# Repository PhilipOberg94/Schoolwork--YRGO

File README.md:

# Schoolwork--YRGO  
**Author**: Philip Öberg

## Overview  
This repository contains various schoolwork assignments and projects completed as part of my studies at YRGO. The focus of these projects is primarily on C++, Python, and C programming languages, with some projects exploring topics like machine learning and signal processing.

## Repository Structure  
The repository is structured into different directories, each containing relevant files and documentation for specific tasks:

- **ML/**: Contains files related to machine learning assignments. Current work includes a linear regression program.
- **Python/**: Contains Python programs showcasing various skills and applications.

## Projects

### Machine Learning (ML)  
- **Linear Regression Program**: A program that demonstrates basic machine learning principles using a simple linear regression model. Data import and manipulation are the main focus areas.

### Python  
- **Automation**: Python scripts for automated systems (e.g., automated horse feeder) and other utility programs.
- **Signal Processing**: Includes a frequency analysis output file (`Frekvensanalys_output.txt`) with updated value labels based on recent changes in signal processing experiments.

## Technologies Used
- C++
- Python
- C

## How to Clone the Repository

To clone the repository, run the following command:

```bash
git clone https://github.com/PhilipOberg94/Schoolwork--YRGO.git

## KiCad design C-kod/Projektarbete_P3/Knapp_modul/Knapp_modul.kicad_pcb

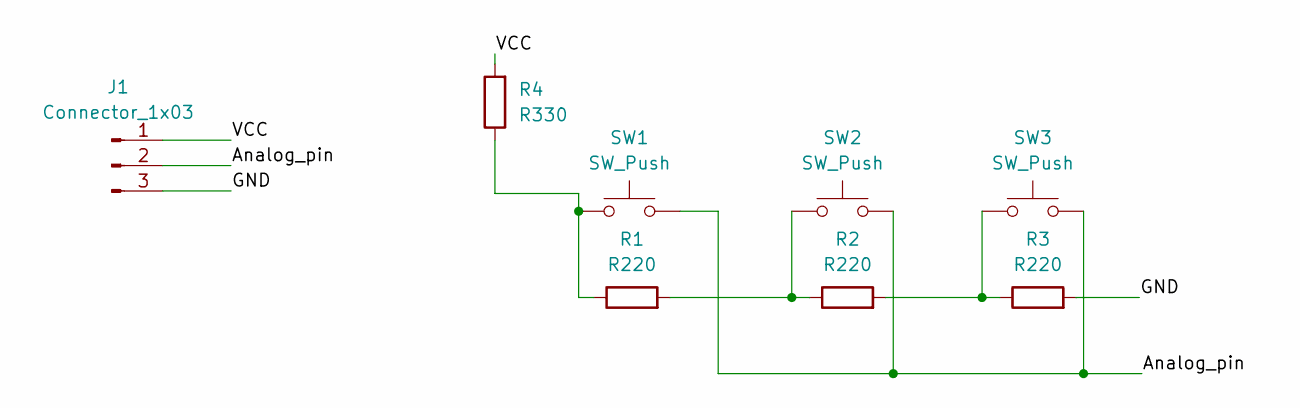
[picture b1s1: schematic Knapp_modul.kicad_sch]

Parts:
J1: Connector_1x03; PinHeader_1x03_P2.54mm_Vertical
R1, R2, R3: R220; R_Axial_DIN0207_L6.3mm_D2.5mm_P10.16mm_Horizontal
R4: R330; R_Axial_DIN0207_L6.3mm_D2.5mm_P10.16mm_Horizontal
SW1, SW2, SW3: SW_Push; LED_D5.0mm

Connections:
/Analog_pin: J1.2, SW1.2, SW2.2, SW3.2
/GND: J1.3, R3.2
/VCC: J1.1, R4.2
unnamed: R1.1, R4.1, SW1.1
unnamed: R1.2, R2.1, SW2.1
unnamed: R2.2, R3.1, SW3.1

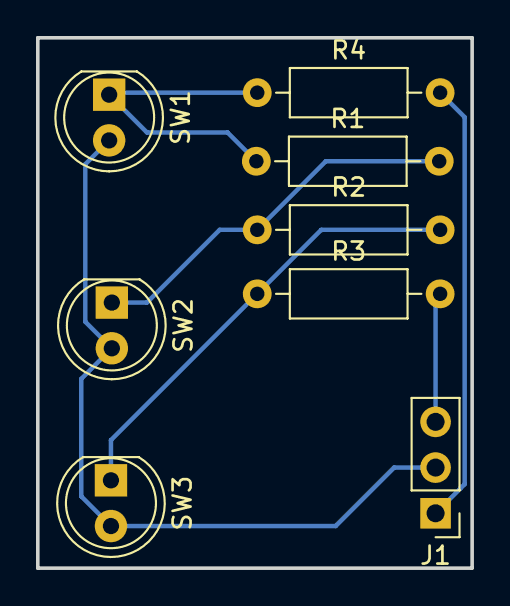
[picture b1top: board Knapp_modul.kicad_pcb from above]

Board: 2 copper layers, 24.1 x 29.5 mm, 8 parts (0 on the bottom side), 6 nets.

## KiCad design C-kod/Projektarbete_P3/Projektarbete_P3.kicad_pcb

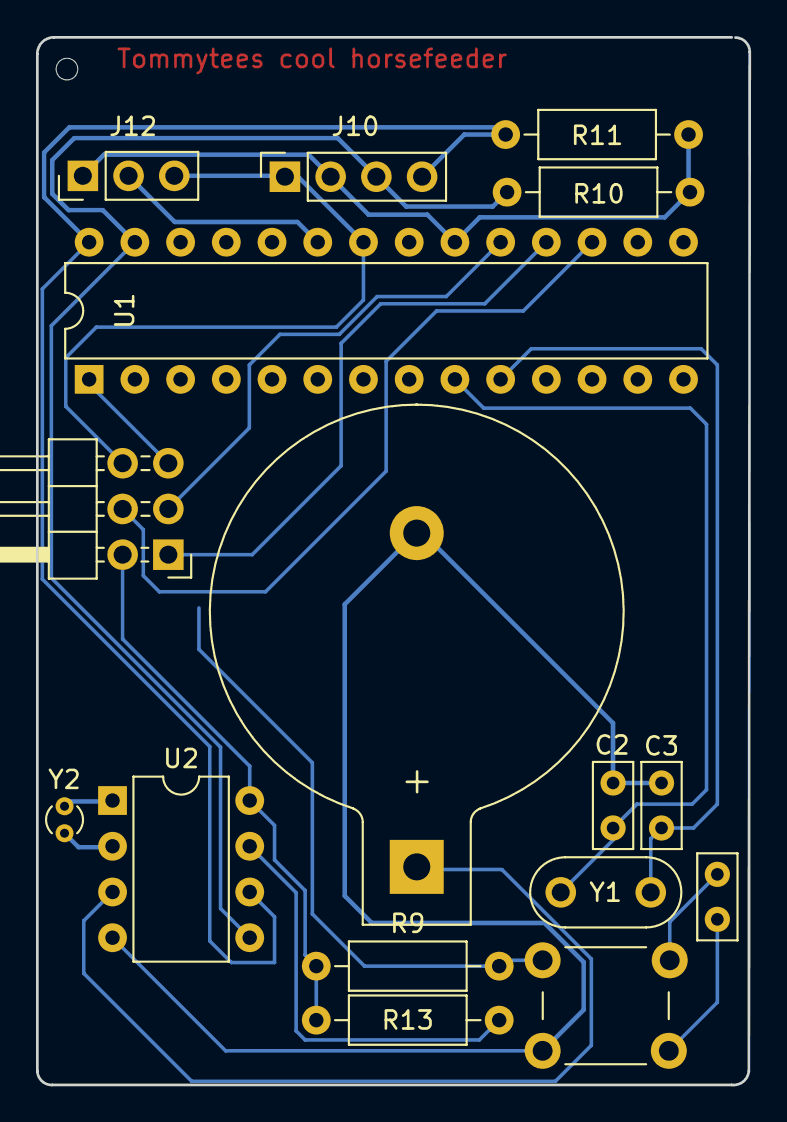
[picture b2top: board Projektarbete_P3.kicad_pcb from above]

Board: 2 copper layers, 39.6 x 58.2 mm, 16 parts (0 on the bottom side), 17 nets.

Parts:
BT1: Battery_Cell; BatteryHolder_Keystone_103_18.54mm
C1: 22nF; C_Rect_L4.6mm_W2.0mm_P2.50mm_MKS02_FKP02
C2, C3: C; C_Rect_L4.6mm_W2.0mm_P2.50mm_MKS02_FKP02
J10: Conn_01x04_LCD-Display; PinSocket_1x04_P2.54mm_Vertical
J11: AVR-ISP-6; PinHeader_2x03_P2.54mm_Horizontal
J12: 3_Button_Conn; PinHeader_1x03_P2.54mm_Vertical
R9: R; R_Axial_DIN0207_L6.3mm_D2.5mm_P10.16mm_Horizontal
R10, R11, R13: R10k; R_Axial_DIN0207_L6.3mm_D2.5mm_P10.16mm_Horizontal
SW1: SW_MEC_5E; SW_PUSH_6mm_H7.3mm_P1
U1: ATmega328-P; DIP-28_W7.62mm
U2: DS1307+; DIP-8_W7.62mm
Y1: Crystal _16Mhz; Resonator-2Pin_W8.0mm_H3.5mm
Y2: Crystal_32kHz; Crystal_DS10_D1.0mm_L4.3mm_Vertical

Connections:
+5V: J10.2, J11.2 (VCC), J12.1, R9.1, R10.1, R11.1, R13.1, U1.7 (VCC), U1.20 (AVCC), U2.8 (VCC)
/AnalogPin0: J12.2, U1.23 (PC0)
/AnalogPin4/SDA: J10.3, R10.2, U1.27 (PC4), U2.5 (SDA)
/AnalogPin5/SCL: J10.4, R11.2, U1.28 (PC5), U2.6 (SCL)
/MISO: J11.1 (MISO), U1.18 (PB4)
/MOSI/OC2A: J11.4 (MOSI), U1.17 (PB3)
/Resetbutton: J11.5 (~RST), R9.2, SW1.3 (K), U1.1 (~RESET/PC6)
/SCK: J11.3 (SCK), U1.19 (PB5)
/X1-Crystal: U2.1 (X1), Y2.2
/X2-Crystal: U2.2 (X2), Y2.1
/XTAL1/TOSC1: C2.1, U1.9 (XTAL1/PB6), Y1.2
/XTAL2/TOSC2: C3.1, U1.10 (XTAL2/PB7), Y1.1
GND: BT1.2 (-), C2.2, C3.2, J10.1, J11.6 (GND), J12.3, SW1.2, U1.8 (GND), U1.22 (GND), U2.4 (GND)
unnamed: BT1.1 (+), U2.3 (VBAT)
unnamed: C1.2, SW1.1
unnamed: C1.1, SW1.4 (A)
unnamed: R13.2, U2.7 (SQW/OUT)

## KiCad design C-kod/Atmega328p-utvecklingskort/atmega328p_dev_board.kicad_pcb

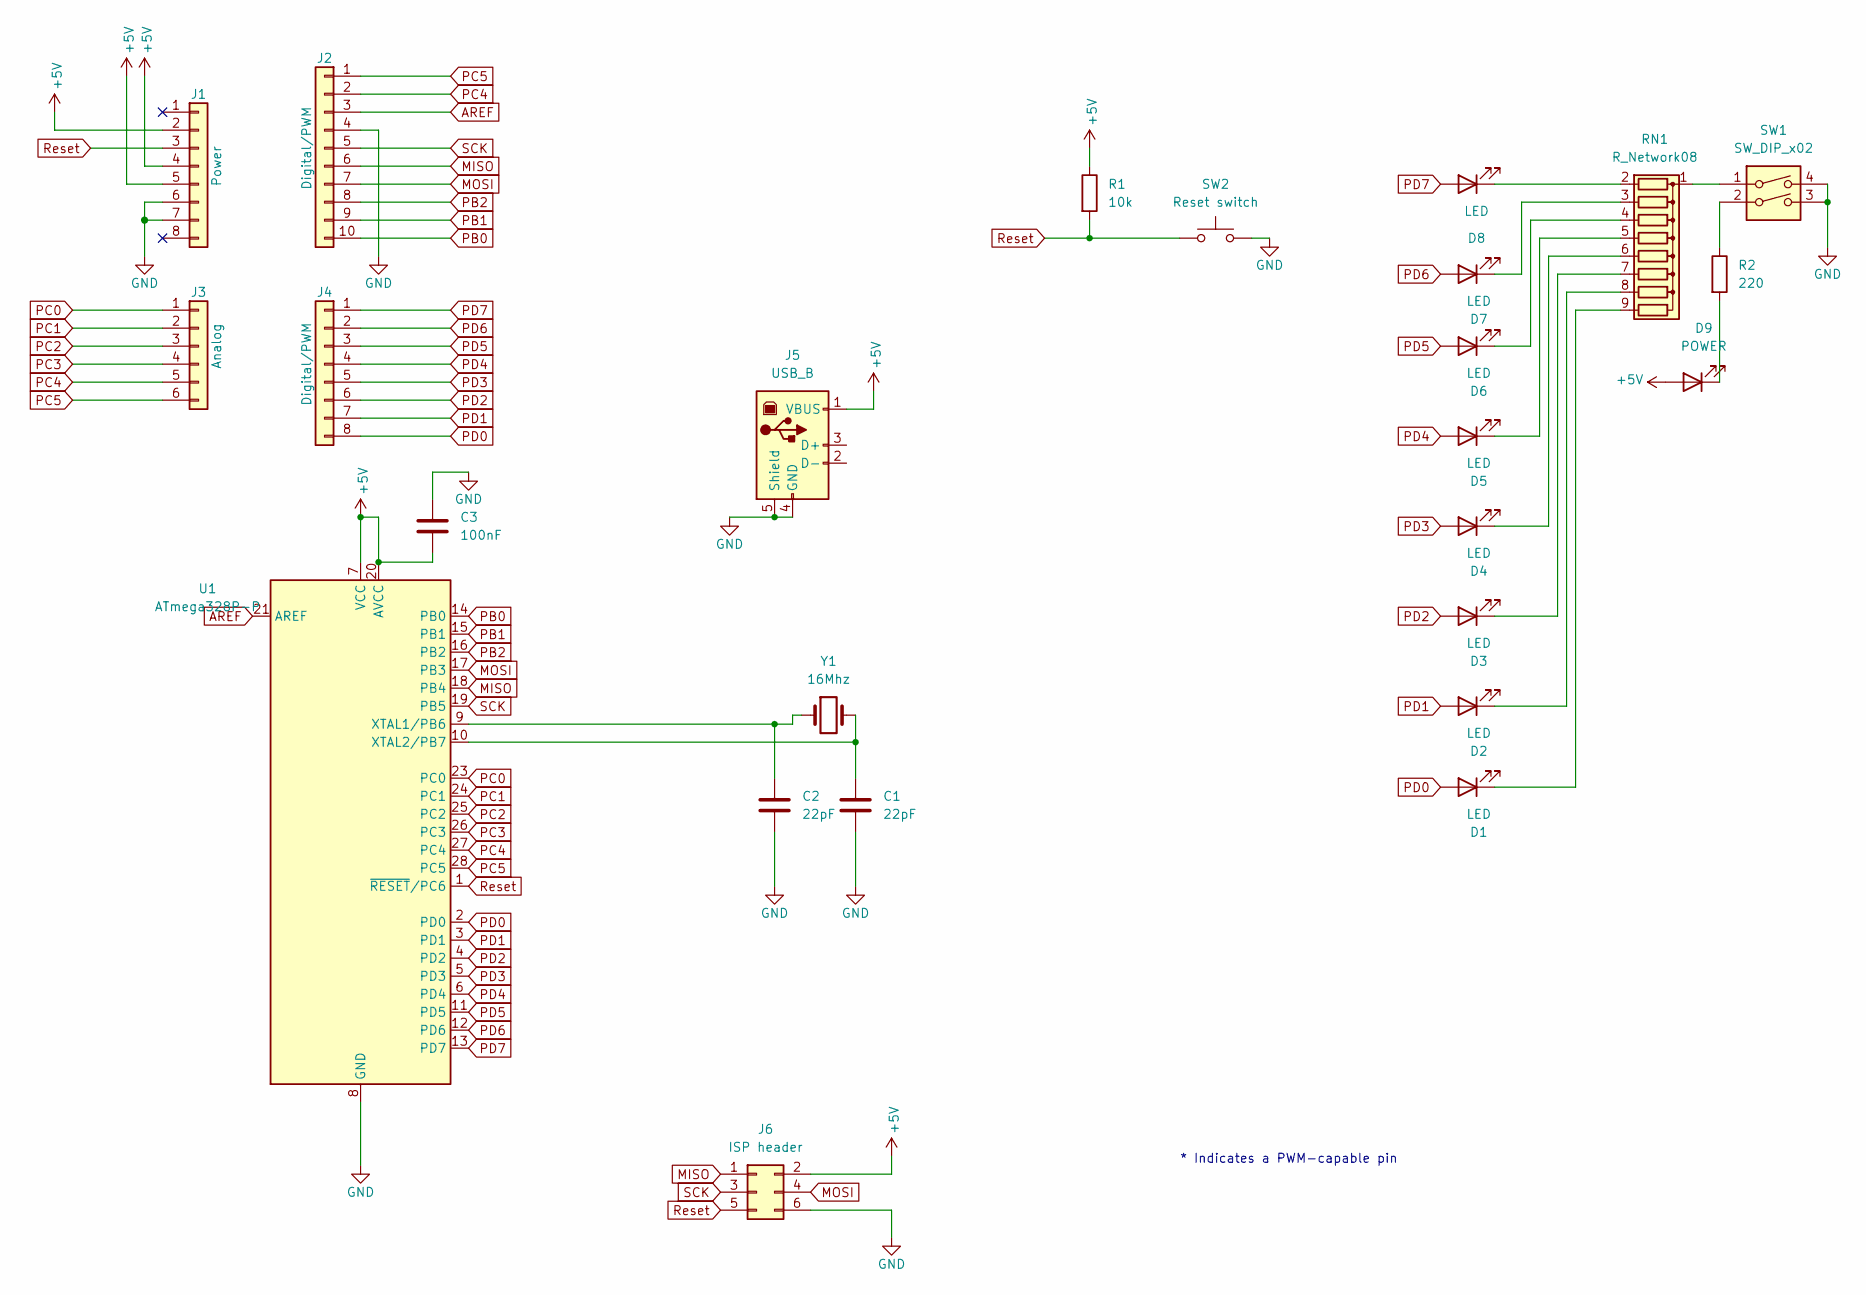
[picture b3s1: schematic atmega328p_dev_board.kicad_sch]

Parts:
C1, C2: 22pF; C_Disc_D5.0mm_W2.5mm_P2.50mm
C3: 100nF; C_Rect_L7.2mm_W2.5mm_P5.00mm_FKS2_FKP2_MKS2_MKP2
D1, D2, D3, D4, D5, D6, D7, D8: LED; LED_D2.0mm_W4.8mm_H2.5mm_FlatTop ändrad
D9: POWER; LED_D5.0mm
J1: Power; PinSocket_1x08_P2.54mm_Vertical
J2: Digital/PWM; PinSocket_1x10_P2.54mm_Vertical
J3: Analog; PinSocket_1x06_P2.54mm_Vertical
J4: Digital/PWM; PinSocket_1x08_P2.54mm_Vertical
J5: USB_B; USB_B_Lumberg_2411_02_Horizontal
J6: ISP header; PinHeader_2x03_P2.54mm_Horizontal
R1: 10k; R_Axial_DIN0207_L6.3mm_D2.5mm_P10.16mm_Horizontal
R2: 220; R_Axial_DIN0207_L6.3mm_D2.5mm_P10.16mm_Horizontal
RN1: R_Network08; R_Array_SIP9
SW1: SW_DIP_x02; DIP-4_W7.62mm
SW2: Reset switch; SW_Tactile_SPST_Angled_PTS645Vx58-2LFS
U1: ATmega328P-P; DIP-28_W7.62mm_Socket_LongPads ovala hål
Y1: 16Mhz; Crystal_HC49-U_Vertical

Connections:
+5V: C3.2, D9.2 (A), J1.2, J1.4, J1.5, J5.1 (VBUS), J6.2, R1.1, U1.7 (VCC), U1.20 (AVCC)
AREF: J2.3, U1.21 (AREF)
GND: C1.2, C2.2, C3.1, J1.6, J1.7, J2.4, J5.4 (GND), J5.5 (Shield), J6.6, SW1.3, SW1.4, SW2.2, U1.8 (GND), U1.22 (GND)
MISO: J2.6, J6.1, U1.18 (PB4)
MOSI: J2.7, J6.4, U1.17 (PB3)
unnamed: D1.1 (K), RN1.9 (R8)
unnamed: D2.1 (K), RN1.8 (R7)
unnamed: D3.1 (K), RN1.7 (R6)
unnamed: D4.1 (K), RN1.6 (R5)
unnamed: D5.1 (K), RN1.5 (R4)
unnamed: D6.1 (K), RN1.4 (R3)
unnamed: D7.1 (K), RN1.3 (R2)
unnamed: D8.1 (K), RN1.2 (R1)
unnamed: D9.1 (K), R2.2
unnamed: R2.1, SW1.2
unnamed: RN1.1 (common), SW1.1
unnamed: C2.1, U1.9 (XTAL1/PB6), Y1.1
unnamed: C1.1, U1.10 (XTAL2/PB7), Y1.2
PB0: J2.10, U1.14 (PB0)
PB1: J2.9, U1.15 (PB1)
PB2: J2.8, U1.16 (PB2)
PC0: J3.1, U1.23 (PC0)
PC1: J3.2, U1.24 (PC1)
PC2: J3.3, U1.25 (PC2)
PC3: J3.4, U1.26 (PC3)
PC4: J2.2, J3.5, U1.27 (PC4)
PC5: J2.1, J3.6, U1.28 (PC5)
PD0: D1.2 (A), J4.8, U1.2 (PD0)
PD1: D2.2 (A), J4.7, U1.3 (PD1)
PD2: D3.2 (A), J4.6, U1.4 (PD2)
PD3: D4.2 (A), J4.5, U1.5 (PD3)
PD4: D5.2 (A), J4.4, U1.6 (PD4)
PD5: D6.2 (A), J4.3, U1.11 (PD5)
PD6: D7.2 (A), J4.2, U1.12 (PD6)
PD7: D8.2 (A), J4.1, U1.13 (PD7)
Reset: J1.3, J6.5, R1.2, SW2.1, U1.1 (~RESET/PC6)
SCK: J2.5, J6.3, U1.19 (PB5)

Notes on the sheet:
* Indicates a PWM-capable pin

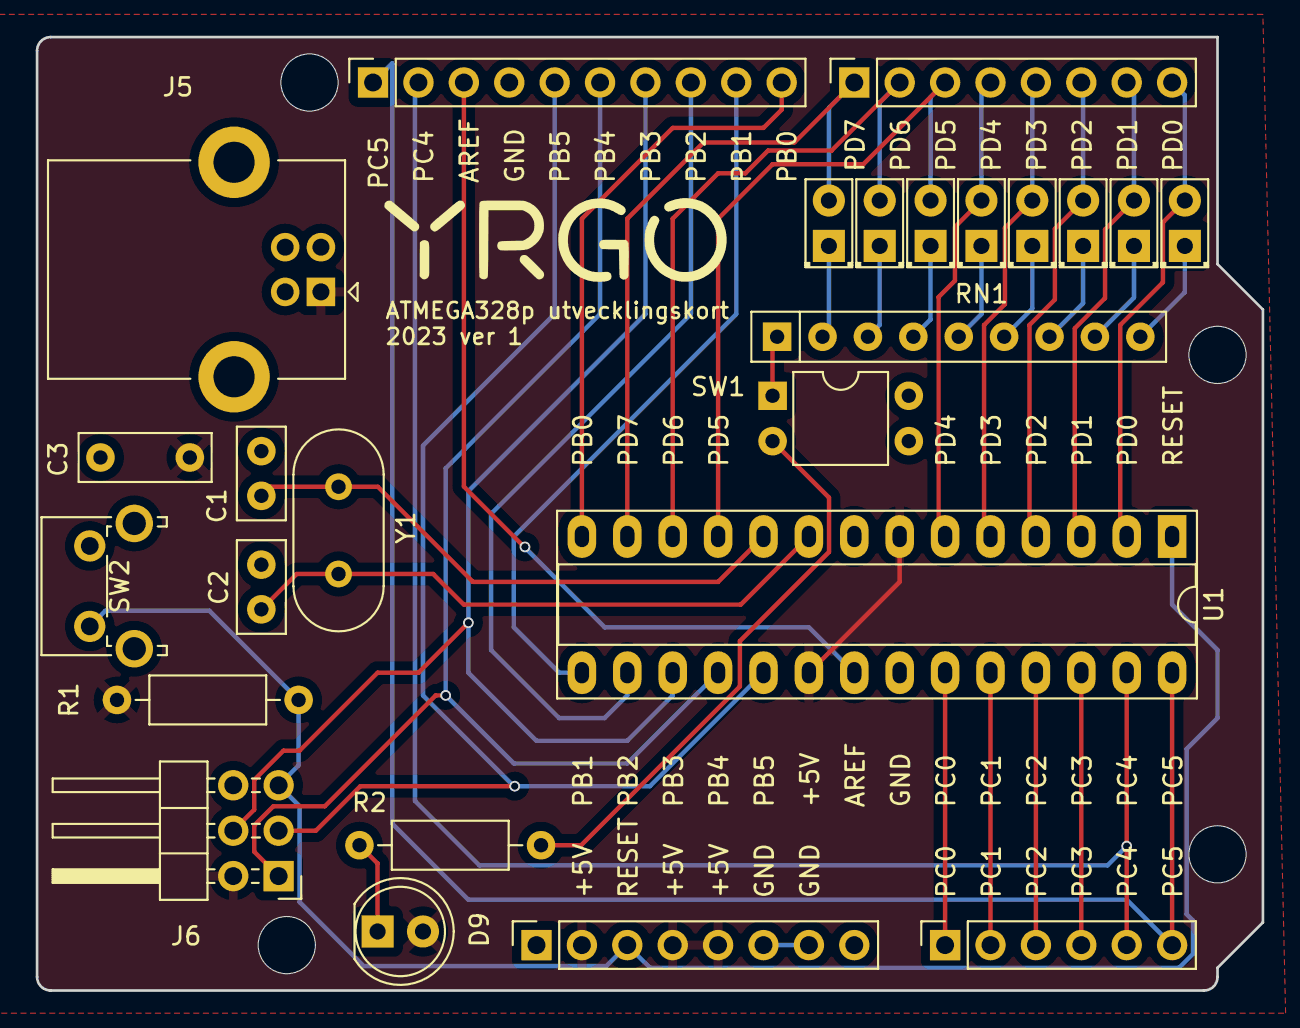
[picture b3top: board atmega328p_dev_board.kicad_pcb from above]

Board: 2 copper layers, 68.6 x 53.3 mm, 29 parts (0 on the bottom side), 37 nets.

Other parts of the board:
MH1, MH2, MH3, MH4: MountingHole_3.2mm

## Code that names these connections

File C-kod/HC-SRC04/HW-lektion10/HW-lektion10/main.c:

/*
* main.c
*
* Created: 1/16/2024 9:16:25 AM
*  Author: JPJ-Engineering
*/
#define F_CPU 1000000UL

#include <avr/io.h>
#include <stdio.h>
#include <util/delay.h>
#include <stdbool.h>
#include <avr/interrupt.h>

#define LCD_DPRT PORTD
#define LCD_DDRD DDRD
#define LCD_DPIN PIND
#define LCD_CPRT PORTB
#define LCD_CDDR DDRB
#define LCD_CPIN PINB
#define LCD_RS 0
#define LCD_RW 1
#define LCD_EN 2
#define BUTTON1 3
#define BUTTON2 4
#define BUTTON3 5

void lcdCOmmand(unsigned char cmnd) {
    LCD_DPRT = cmnd;
    LCD_CPRT &= ~ (1<<LCD_RS);
    LCD_CPRT &= ~ (1<<LCD_RW);
    LCD_CPRT |= (1<<LCD_EN);
    _delay_us(10);
    LCD_CPRT &= ~(1<<LCD_EN);
    _delay_us(3000);
}

void lcdData(unsigned char data) {
    LCD_DPRT = data;
    LCD_CPRT |= (1<<LCD_RS);
    LCD_CPRT &= ~ (1<<LCD_RW);
    LCD_CPRT |= (1<<LCD_EN);
    _delay_us(10);
    LCD_CPRT &= ~ (1<<LCD_EN);
    _delay_us(3000);
}

bool sw1 (){
    if (PINB & (1<<BUTTON1)) {
        return false;
    }
    else return true;
}
bool sw2 (){
    if (PINB & (1<<BUTTON2)) {
        return false;
    }
    else return true;
}
bool sw3 (){
    if (PINB & (1<<BUTTON3)) {
        return false;
    }
    else return true;
}


void lcd_init() {
    LCD_DDRD = 0xFF;
    LCD_CDDR = 0b00000111;
    PORTB = 0b00111000;
    
    LCD_CPRT &=~(1<<LCD_EN);
    _delay_us(2000);
    lcdCOmmand(0x38);
    lcdCOmmand(0x0E);
    lcdCOmmand(0x01);
    _delay_us(2000);
    lcdCOmmand(0x06);
    
    DDRC = 0xFF;							// Port C all output. PC0: RW		PC1: RS		PC2: E
    DDRC &= ~(1<<DDC5);						// Set Pin C5 as input to read Echo
    PORTC |= (1<<PORTC5);					// Enable pull up on C5
    PORTC &= ~(1<<PC4);						// Init C4 as low (trigger)

    PRR &= ~(1<<PRTIM1);					// To activate timer1 module
    TCNT1 = 0;								// Initial timer value
    TCCR1B |= (1<<CS10);					// Timer without prescaller. Since default clock for atmega328p is 1Mhz period is 1uS
    TCCR1B |= (1<<ICES1);					// First capture on rising edge

    PCICR = (1<<PCIE1);						// Enable PCINT[14:8] we use pin C5 which is PCINT13
    PCMSK1 = (1<<PCINT13);					// Enable C5 interrupt
    sei();
}

void lcd_gotoxy(unsigned char x, unsigned char y) {
    unsigned char firstCharAdr[] = {0x80,0xC0,0x94,0xD4};
    lcdCOmmand(firstCharAdr[y-1]+x-1);
    _delay_ms(1);
}

void lcd_print(char * str) {
    unsigned char i = 0;
    
    while(str[i] != 0) {
        lcdData(str[i]);
        i++;
    }
}
int main(void)
{
    lcd_init();
    
    
    while(1){
        
        
        _delay_ms(60); 							// To allow sufficient time between queries (60ms min)

        PORTC |= (1<<PC4);						// Set trigger high
        _delay_us(10);							// for 10uS
        PORTC &= ~(1<<PC4);						// to trigger the ultrasonic module
    }
}
/*******************************************INTURRUPT PCINT1 FOR PIN C5*******************************************/
char result [6];

ISR(PCINT1_vect) {
    if (bit_is_set(PINC,PC5)) {					// Checks if echo is high
        TCNT1 = 0;								// Reset Timer
        PORTC |= (1<<PC3);
        } else {
        uint32_t numuS = TCNT1;					// Save Timer value
        uint16_t oldSREG = SREG;
       
        char temp [6];
        sprintf(temp, "%d",(int) roundf (numuS/58));
        
        for (int i = 0; i < sizeof(temp);i++) {
            if (result[i] != temp[i]) {
                
        lcdCOmmand(1);
            }
            result [i] = temp [i];
        }
        
         lcd_gotoxy(1,1);
        lcd_print("CM: ");
         lcd_gotoxy(5,1);
        lcd_print(result);
        _delay_us(250);
        SREG = oldSREG;
						// Enable interrupts
    }
}

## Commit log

2024-09-10 Add Python folder with initial files
2024-09-11 Changes to low_pass
2024-09-11 Finished code for Lab
2024-09-12 Remove of duplicated dir
2024-09-12 Adding "Kapitel 8" to main
2024-09-12 Removing myenv dir
2024-09-12 Removed myenv dir
2024-09-12 Add all files to the repository
2024-09-12 Added troubleshooting and simplifying the code
2024-09-12 Changes to structure
2024-09-12 Ändringar i kapitel 8
2024-09-16 Changes to Inlämning #3
2024-09-17 Update .gitignore
    added myenv
2024-09-17 Made a C++ dir
2024-09-17 Changes to Labration - Frekvensanalys.py
2024-09-18 Import a dir for lin_reg program
2024-09-18 Changes made to Frekvensanalys
2024-09-18 Changes made for presenting data
2024-09-18 Changes to name of outputfile
2024-09-18 Commentary updated
2024-09-19 Changes to value labels
2024-09-19 Small changes to the Frekvensanalys program
2024-09-23 Python code updated
2024-09-23 Updated gitignore file
2024-09-24 Updated the commentary
2024-09-24 Updated commentary
2024-09-24 Erased .txt file
2024-09-26 Updated horsefeeder program
2024-10-02 Remove Zone.Indentifier files
2024-10-02 Updated to the new LCD
2024-10-02 Deleted atmega project in ML
2024-10-02 Changes made to i2c_lcd and rtc to work with the display
2024-10-06 Changes to the filter calculations
2024-10-06 Representation of H corrected
2024-10-06 Moved output file
2024-10-07 Create LICENSE
2024-10-11 Updated with previous programs and code
2024-10-22 Changes made to be able to change boxes and time
2025-03-05 Updated rtc.py, now a working version
2025-03-17 Changed to manage the project in one file
2025-03-17 changed rtc.py yo function with ds3231 chip instead
2025-03-18 Update horse_feeder.py with OFF function for boxes
2025-03-27 Added a TCP_client for comm with Pico
2025-03-28 Updated with the new relaymodule and network connection
